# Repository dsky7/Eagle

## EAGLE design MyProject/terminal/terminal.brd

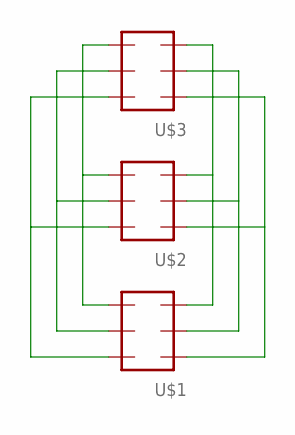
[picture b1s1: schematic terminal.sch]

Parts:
U$1, U$2, U$3: PIN_HEADER_32; PIN_HEADER_3*2

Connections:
unnamed: U$1.P$3 (3), U$2.P$3 (3), U$3.P$3 (3)
unnamed: U$1.P$2 (2), U$2.P$2 (2), U$3.P$2 (2)
unnamed: U$1.P$1 (1), U$2.P$1 (1), U$3.P$1 (1)
unnamed: U$1.P$6 (6), U$2.P$6 (6), U$3.P$6 (6)
unnamed: U$1.P$5 (5), U$2.P$5 (5), U$3.P$5 (5)
unnamed: U$1.P$4 (4), U$2.P$4 (4), U$3.P$4 (4)

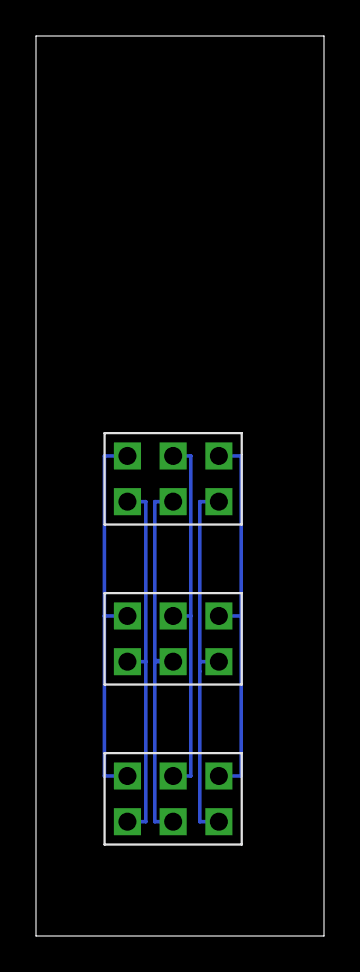
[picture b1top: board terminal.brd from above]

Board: 2 copper layers, 16.0 x 50.0 mm, 3 parts (0 on the bottom side), 6 nets.

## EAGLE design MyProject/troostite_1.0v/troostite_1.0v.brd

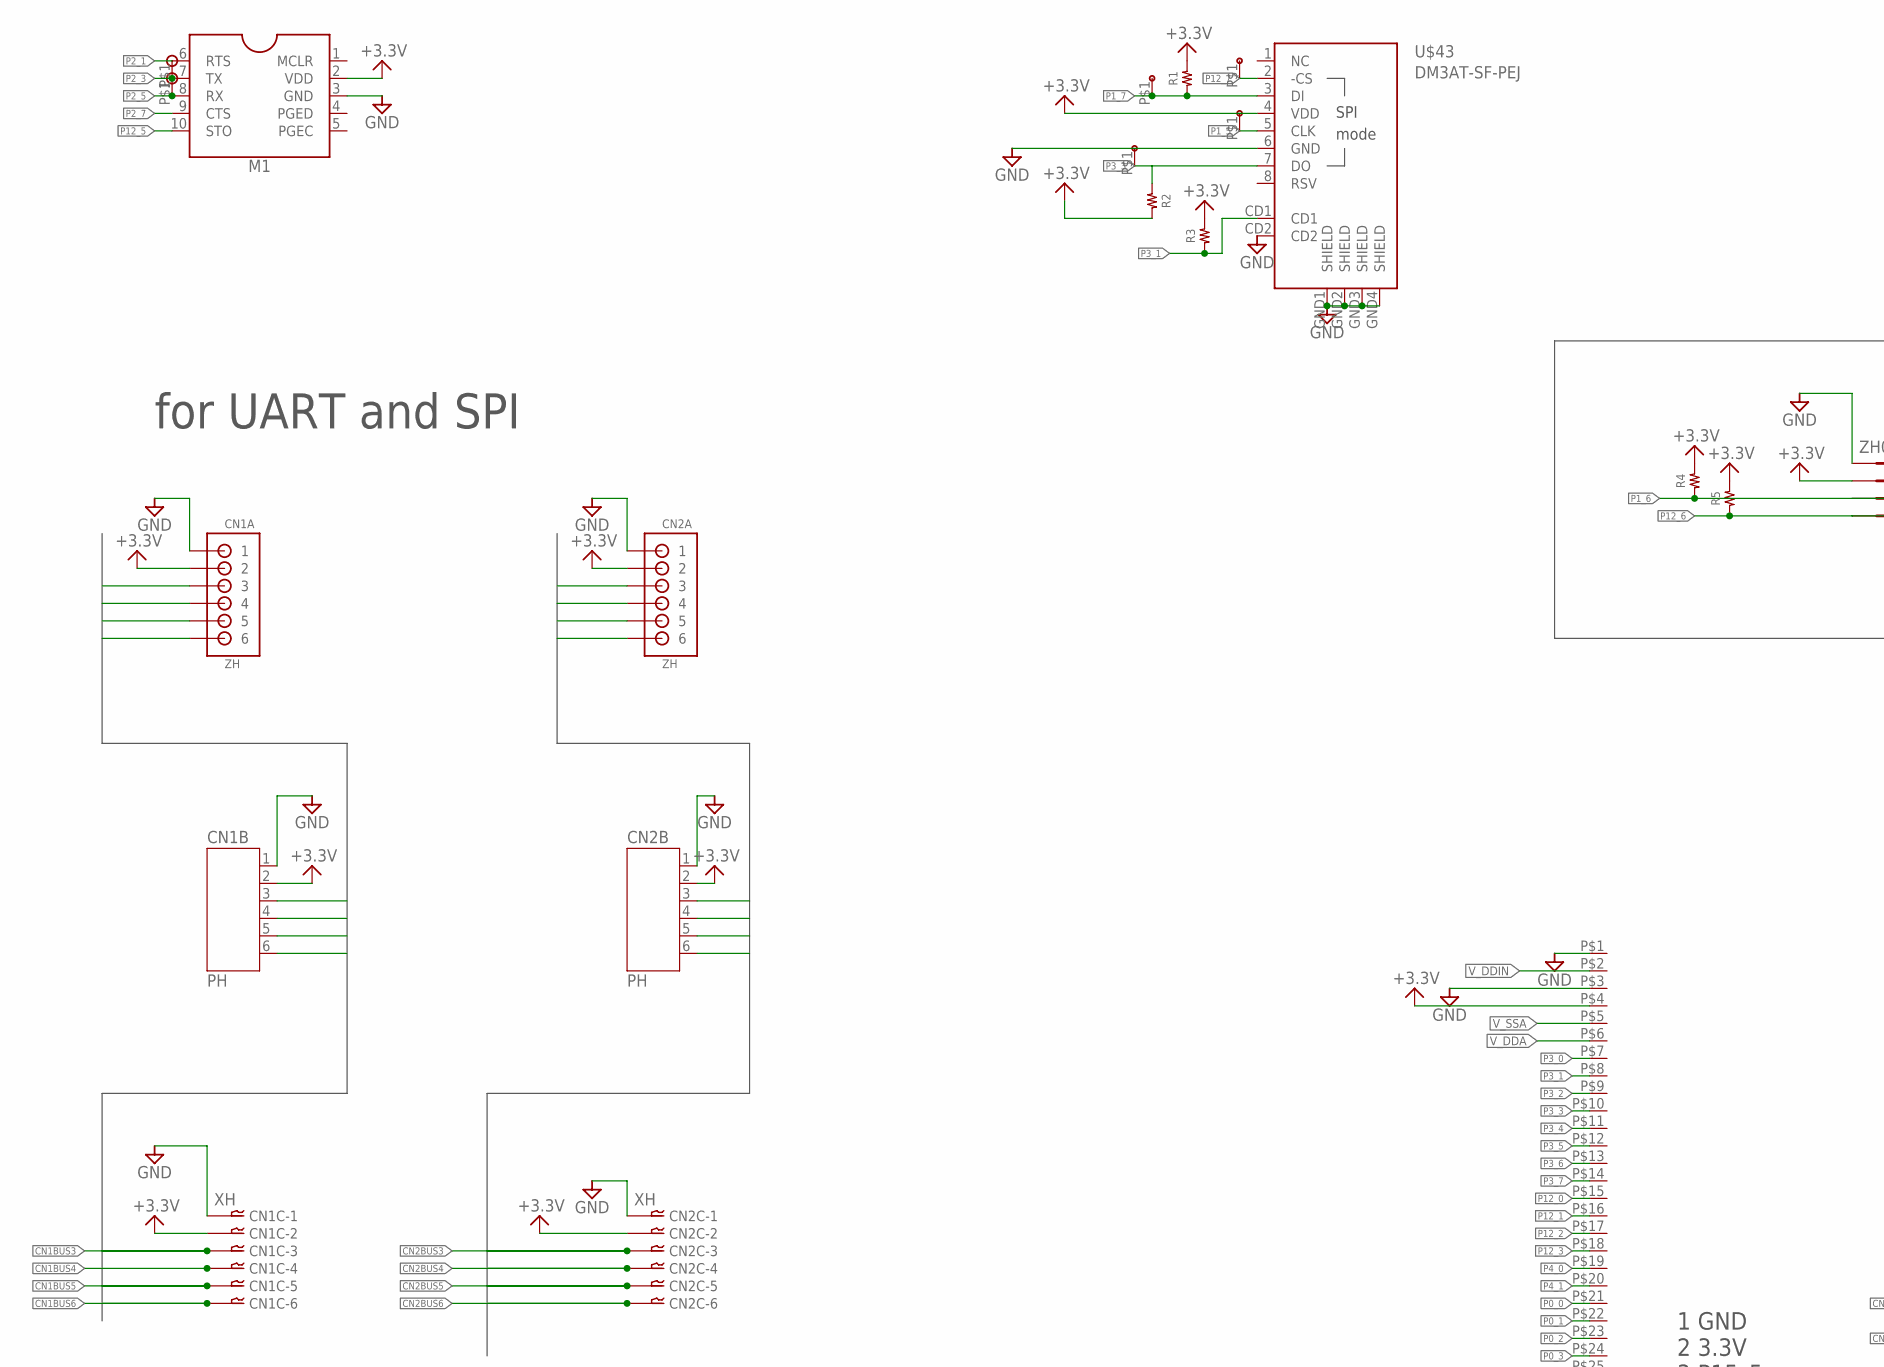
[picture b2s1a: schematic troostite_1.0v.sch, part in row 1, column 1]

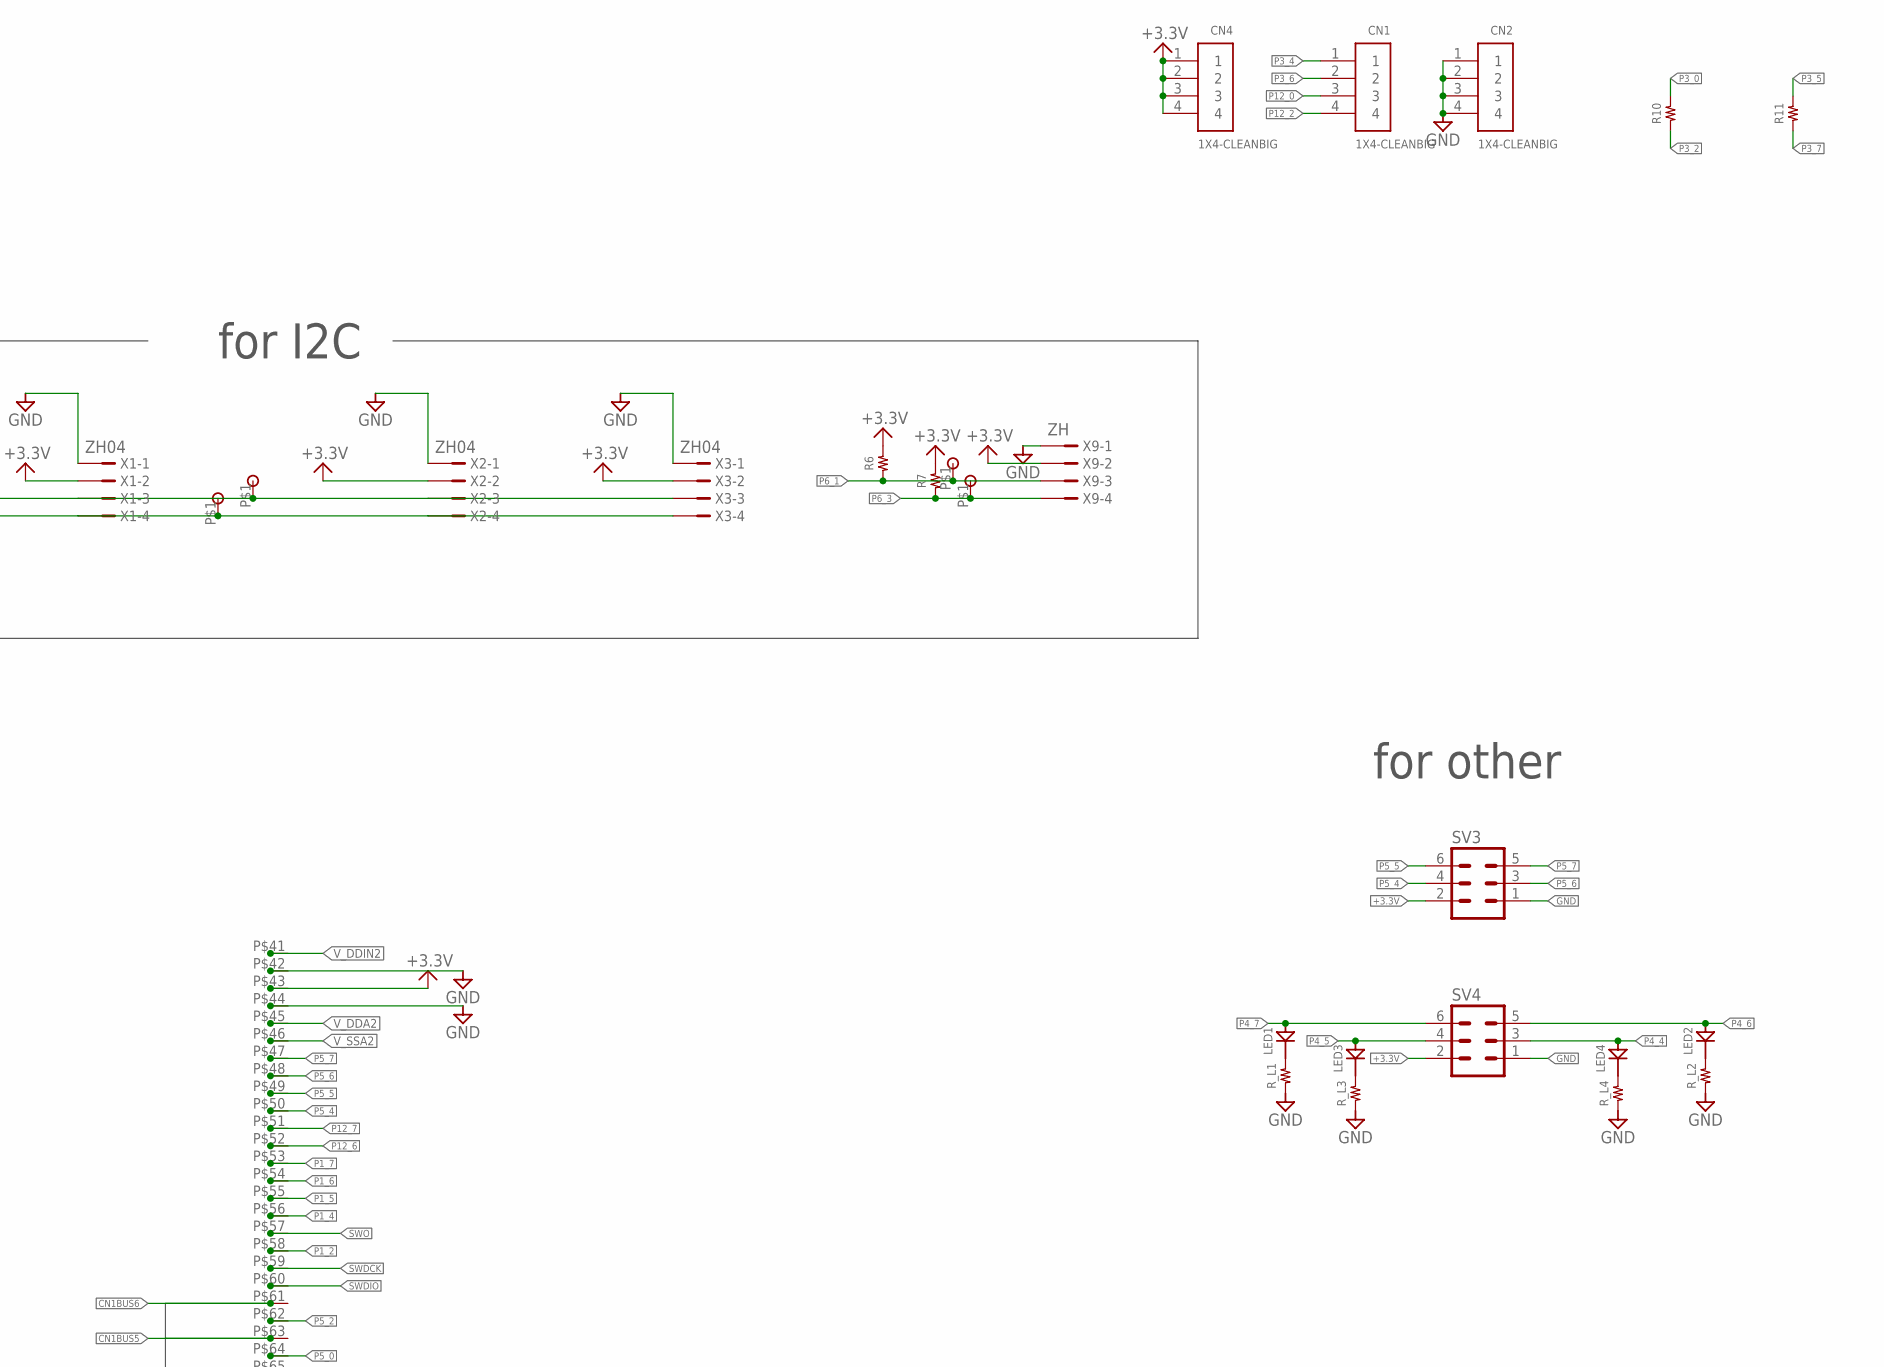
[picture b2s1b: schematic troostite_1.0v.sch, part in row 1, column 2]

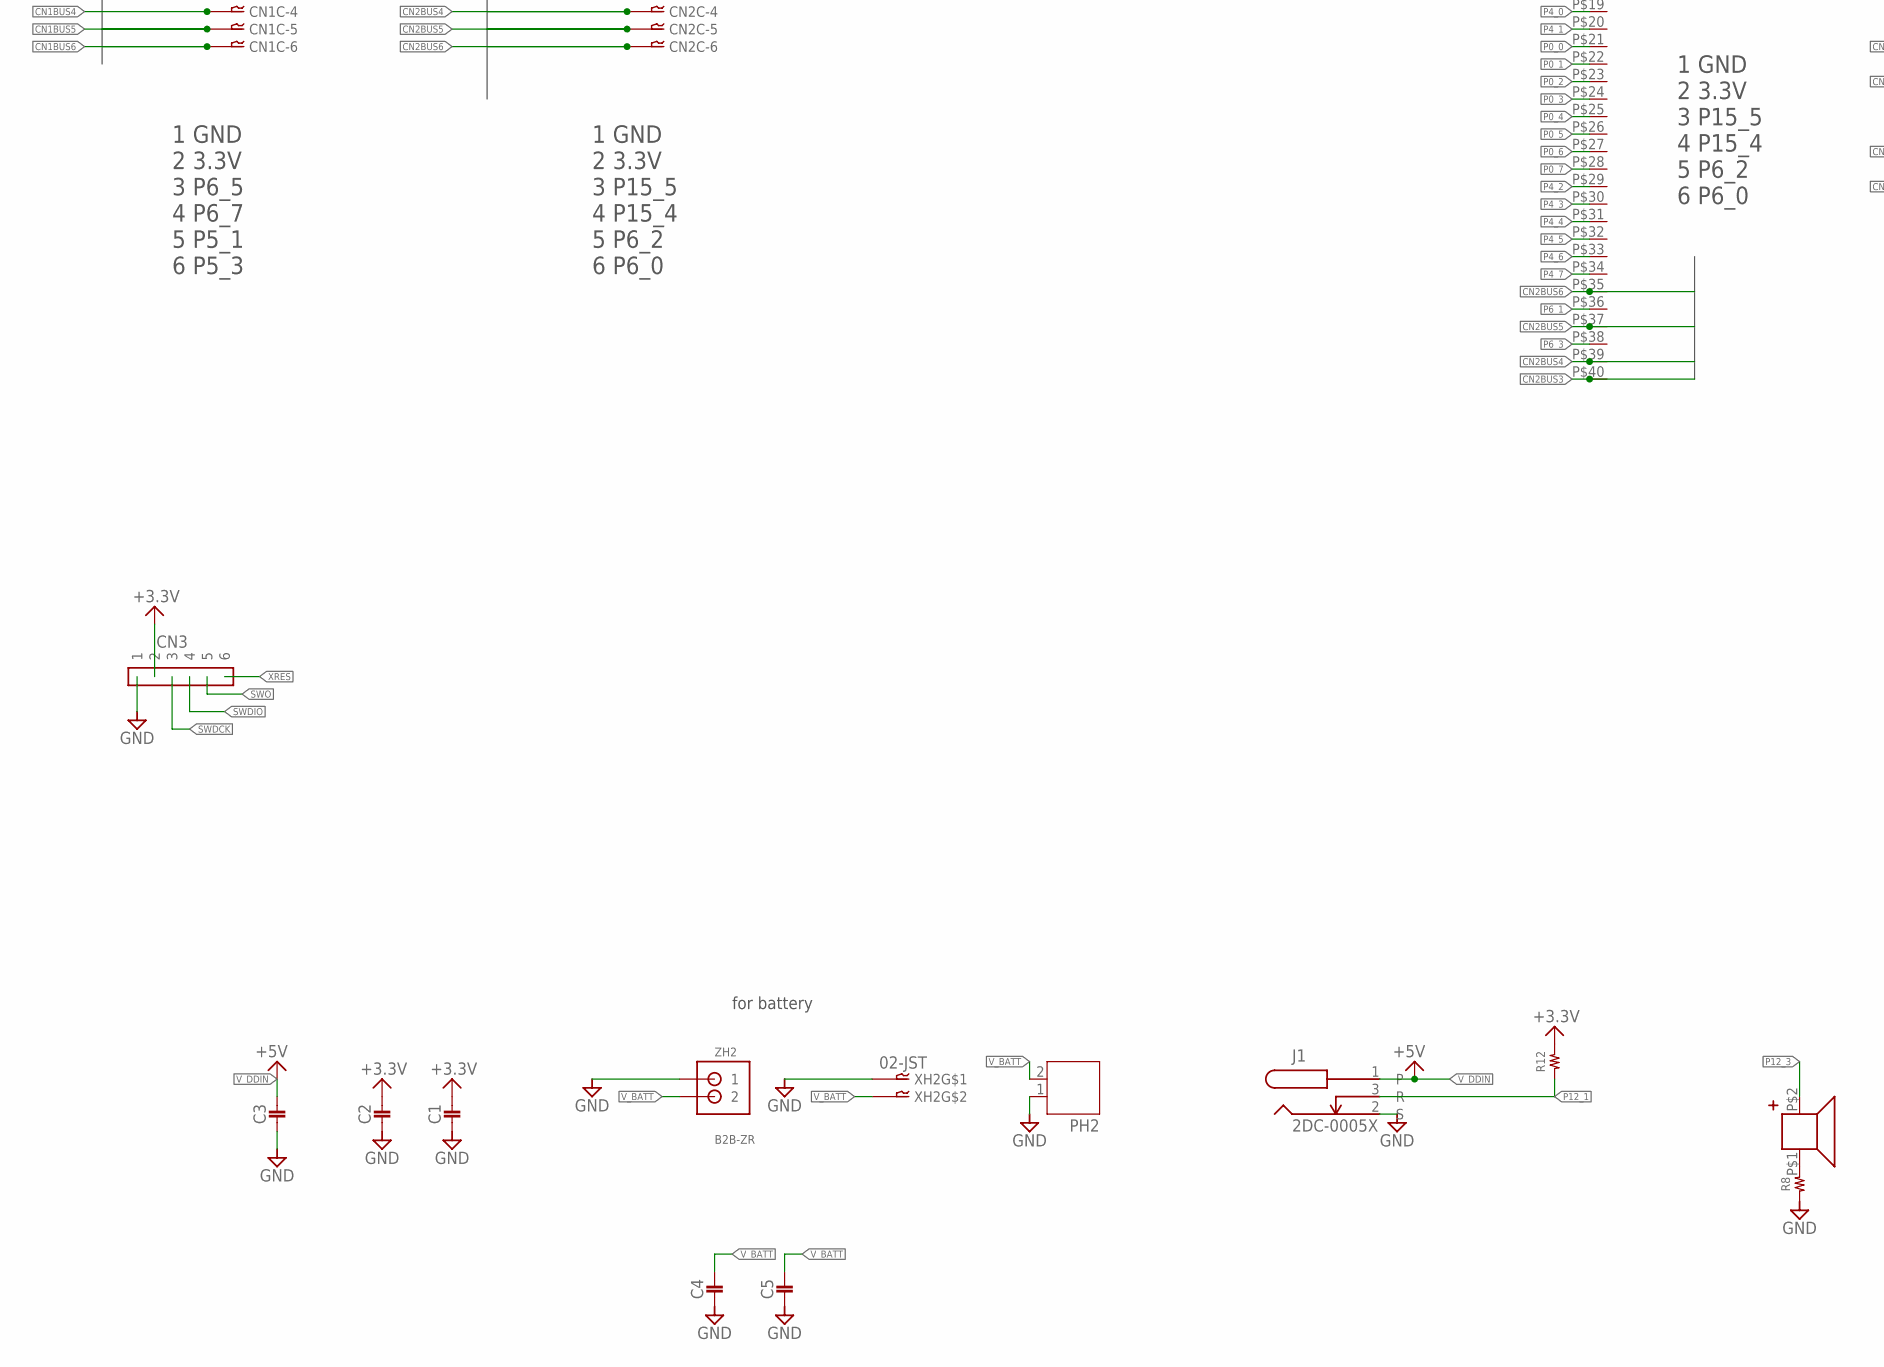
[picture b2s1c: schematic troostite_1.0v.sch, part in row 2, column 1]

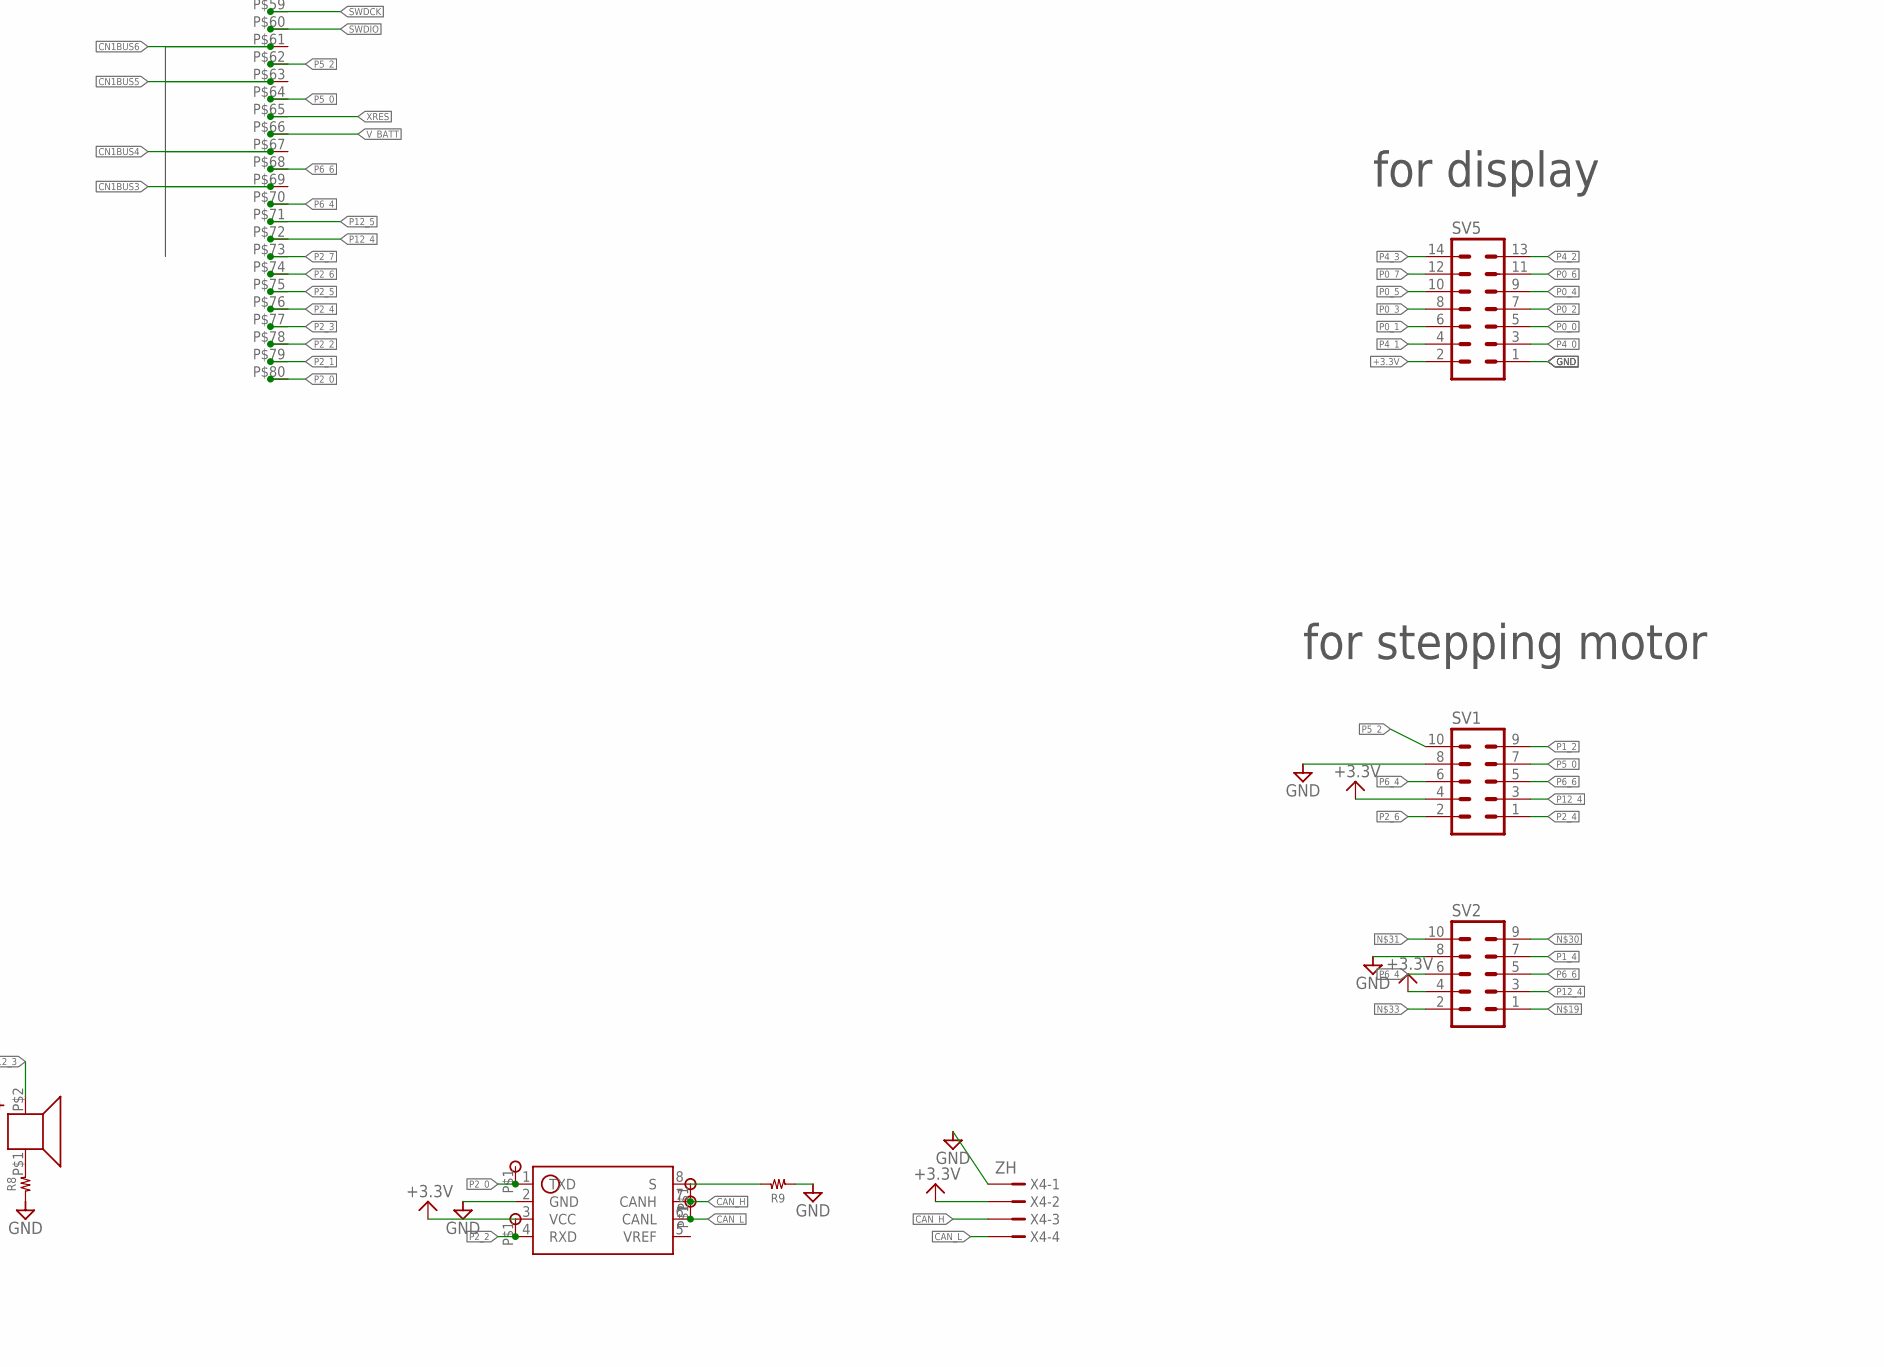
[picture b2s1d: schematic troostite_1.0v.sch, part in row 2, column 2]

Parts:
C1, C2, C3, C4: 1608
C5: 3225
CN1, CN2, CN4: 1X4-CLEANBIG; 1X04-CLEANBIG
CN1A, CN2A: ZH; B6B-ZR
CN1B, CN2B: PH; JST-PH6
CN1C, CN2C: XH; B6B-XH
CN3: PIN_HEADER_6
IC1: SN65HVD1050; SOIC8
J1: 2DC-0005X; 2DC-0005D
LED1, LED2, LED3, LED4: CHIPLED; 1608
M1: SBDBT; DIL10
PH2: JST-PH2
R1, R2, R3, R4, R5, R6, R7, R8, R9, R10, R11, R12: RESISTOR__SMD; 1608
R_L1, R_L2, R_L3, R_L4: RESISTOR__SMD; 1608
SV1, SV2: ML10
SV3, SV4: ML6
SV5: ML14
U$2: PSOC_5LP
U$41: PKLCS1212E4001
U$43: DM3AT-SF-PEJ
U$72, U$73, U$74, U$75, U$76, U$77, U$78, U$79, U$82, U$83: CHECK_0.8MM
U$85, U$86, U$87, U$88: CHECK_21.3; CHECK_2*1.3
X1, X2, X3: ZH04; B4B-ZR
X4, X9: ZH; B4B-ZR
XH2: 02-JST; B2B-XH
ZH2: B2B-ZR

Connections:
+3.3V: C1.P$1 (1), C2.P$1 (1), CN1A.2, CN1B.2, CN1C.P$2, CN2A.2, CN2B.2, CN2C.P$2, CN3.2, CN4.1, CN4.2, CN4.3, CN4.4, IC1.3 (VCC), M1.2 (VDD), R1.2, R2.2, R3.2, R4.2, R5.2, R6.2, R7.2, R12.2, SV1.4, SV2.4, SV3.2, SV4.2, SV5.2, U$2.P$4, U$2.P$43, U$43.4 (VDD), X1.2, X2.2, X3.2, X4.2, X9.2
CAN_H: IC1.7 (CANH), U$72.P$1, X4.3
CAN_L: IC1.6 (CANL), U$73.P$1, X4.4
CN1BUS3: CN1A.3, CN1B.3, CN1C.P$3, U$2.P$69
CN1BUS4: CN1A.4, CN1B.4, CN1C.P$4, U$2.P$67
CN1BUS5: CN1A.5, CN1B.5, CN1C.P$5, U$2.P$63
CN1BUS6: CN1A.6, CN1B.6, CN1C.P$6, U$2.P$61
CN2BUS3: CN2A.3, CN2B.3, CN2C.P$3, U$2.P$40
CN2BUS4: CN2A.4, CN2B.4, CN2C.P$4, U$2.P$39
CN2BUS5: CN2A.5, CN2B.5, CN2C.P$5, U$2.P$37
CN2BUS6: CN2A.6, CN2B.6, CN2C.P$6, U$2.P$35
GND: C1.P$2 (2), C2.P$2 (2), C3.P$2 (2), C4.P$2 (2), C5.P$2 (2), CN1A.1, CN1B.1, CN1C.P$1, CN2.1, CN2.2, CN2.3, CN2.4, CN2A.1, CN2B.1, CN2C.P$1, CN3.1, IC1.2 (GND), J1.2 (S), M1.3 (GND), PH2.1, R8.1, R9.1, R_L1.1, R_L2.1, R_L3.1, R_L4.1, SV1.8, SV2.8, SV3.1, SV4.1, SV5.1, U$2.P$1, U$2.P$3, U$2.P$42, U$2.P$44, U$43.6 (GND), U$43.CD2, U$43.GND1 (SHIELD), U$43.GND2 (SHIELD), U$43.GND3 (SHIELD), U$43.GND4 (SHIELD), X1.1, X2.1, X3.1, X4.1, X9.1, XH2.P$1, ZH2.1
unnamed: R8.2, U$41.P$1 (MINUS)
unnamed: LED1.2 (K), R_L1.2
unnamed: LED3.2 (K), R_L3.2
unnamed: LED4.2 (K), R_L4.2
unnamed: LED2.2 (K), R_L2.2
unnamed: IC1.8 (S), R9.2
P0_0: SV5.5, U$2.P$21
P0_1: SV5.6, U$2.P$22
P0_2: SV5.7, U$2.P$23
P0_3: SV5.8, U$2.P$24
P0_4: SV5.9, U$2.P$25
P0_5: SV5.10, U$2.P$26
P0_6: SV5.11, U$2.P$27
P0_7: SV5.12, U$2.P$28
P1_2: SV1.9, U$2.P$58
P1_4: SV2.7, U$2.P$56
P1_5: U$2.P$55, U$43.5 (CLK), U$87.P$1
P1_6: R4.1, U$2.P$54, U$76.P$1, X1.3, X2.3, X3.3
P1_7: R1.1, U$2.P$53, U$43.3 (DI), U$85.P$1
P2_0: IC1.1 (TXD), U$2.P$80, U$74.P$1
P2_1: M1.6 (RTS), U$2.P$79
P2_2: IC1.4 (RXD), U$2.P$78, U$75.P$1
P2_3: M1.7 (TX), U$2.P$77, U$82.P$1
P2_4: SV1.1, U$2.P$76
P2_5: M1.8 (RX), U$2.P$75, U$83.P$1
P2_6: SV1.2, U$2.P$74
P2_7: M1.9 (CTS), U$2.P$73
P3_0: R10.2, U$2.P$7
P3_1: R3.1, U$2.P$8, U$43.CD1
P3_2: R10.1, U$2.P$9
P3_3: R2.1, U$2.P$10, U$43.7 (DO), U$88.P$1
P3_4: CN1.1, U$2.P$11
P3_5: R11.2, U$2.P$12
P3_6: CN1.2, U$2.P$13
P3_7: R11.1, U$2.P$14
P4_0: SV5.3, U$2.P$19
P4_1: SV5.4, U$2.P$20
P4_2: SV5.13, U$2.P$29
P4_3: SV5.14, U$2.P$30
P4_4: LED4.1 (A), SV4.3, U$2.P$31
P4_5: LED3.1 (A), SV4.4, U$2.P$32
P4_6: LED2.1 (A), SV4.5, U$2.P$33
P4_7: LED1.1 (A), SV4.6, U$2.P$34
P5_0: SV1.7, U$2.P$64
P5_2: SV1.10, U$2.P$62
P5_4: SV3.4, U$2.P$50
P5_5: SV3.6, U$2.P$49
P5_6: SV3.3, U$2.P$48
P5_7: SV3.5, U$2.P$47
P6_1: R6.1, U$2.P$36, U$78.P$1, X9.3
P6_3: R7.1, U$2.P$38, U$79.P$1, X9.4
P6_4: SV1.6, SV2.6, U$2.P$70
P6_6: SV1.5, SV2.5, U$2.P$68
P12_0: CN1.3, U$2.P$15
P12_1: J1.3 (R), R12.1, U$2.P$16
P12_2: CN1.4, U$2.P$17
P12_3: U$2.P$18, U$41.P$2 (PLUS)
P12_4: SV1.3, SV2.3, U$2.P$72
P12_5: M1.10 (STO), U$2.P$71
P12_6: R5.1, U$2.P$52, U$77.P$1, X1.4, X2.4, X3.4
P12_7: U$2.P$51, U$43.2 (-CS), U$86.P$1
SWDCK: CN3.3, U$2.P$59
SWDIO: CN3.4, U$2.P$60
SWO: CN3.5, U$2.P$57
V_BATT: C4.P$1 (1), C5.P$1 (1), PH2.2, U$2.P$66, XH2.P$2, ZH2.2
V_DDA: U$2.P$6
V_DDA2: U$2.P$45
V_DDIN: C3.P$1 (1), J1.1, U$2.P$2
V_DDIN2: U$2.P$41
V_SSA: U$2.P$5
V_SSA2: U$2.P$46
XRES: CN3.6, U$2.P$65

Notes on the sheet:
for stepping motor
for other
for battery
for UART and SPI
for I2C
for display
1 GND 2 3.3V 3 P6_5 4 P6_7 5 P5_1 6 P5_3
1 GND 2 3.3V 3 P15_5 4 P15_4 5 P6_2 6 P6_0

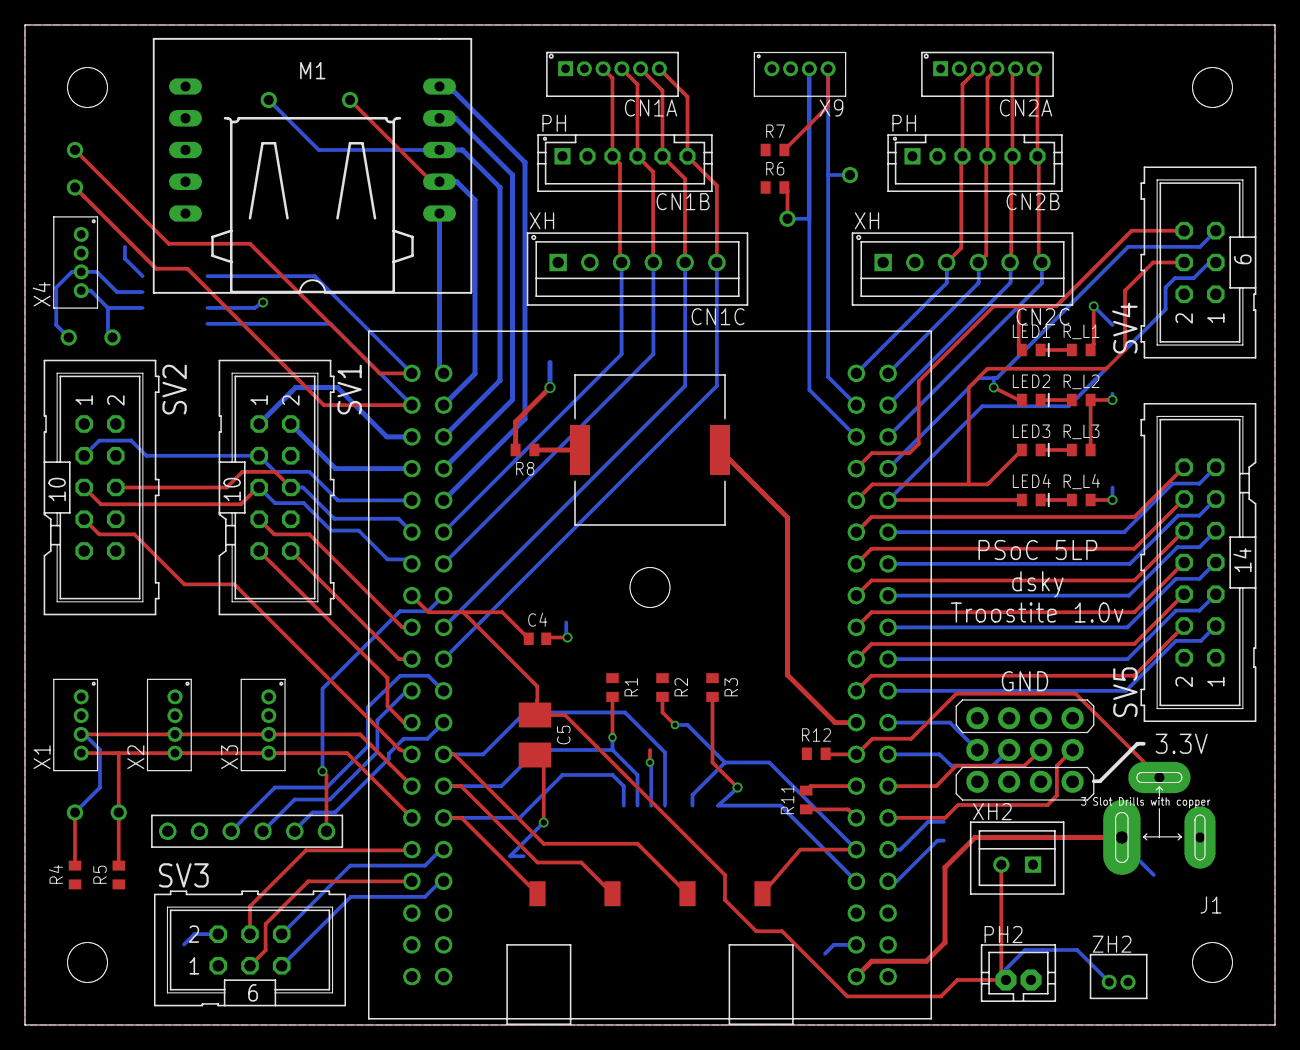
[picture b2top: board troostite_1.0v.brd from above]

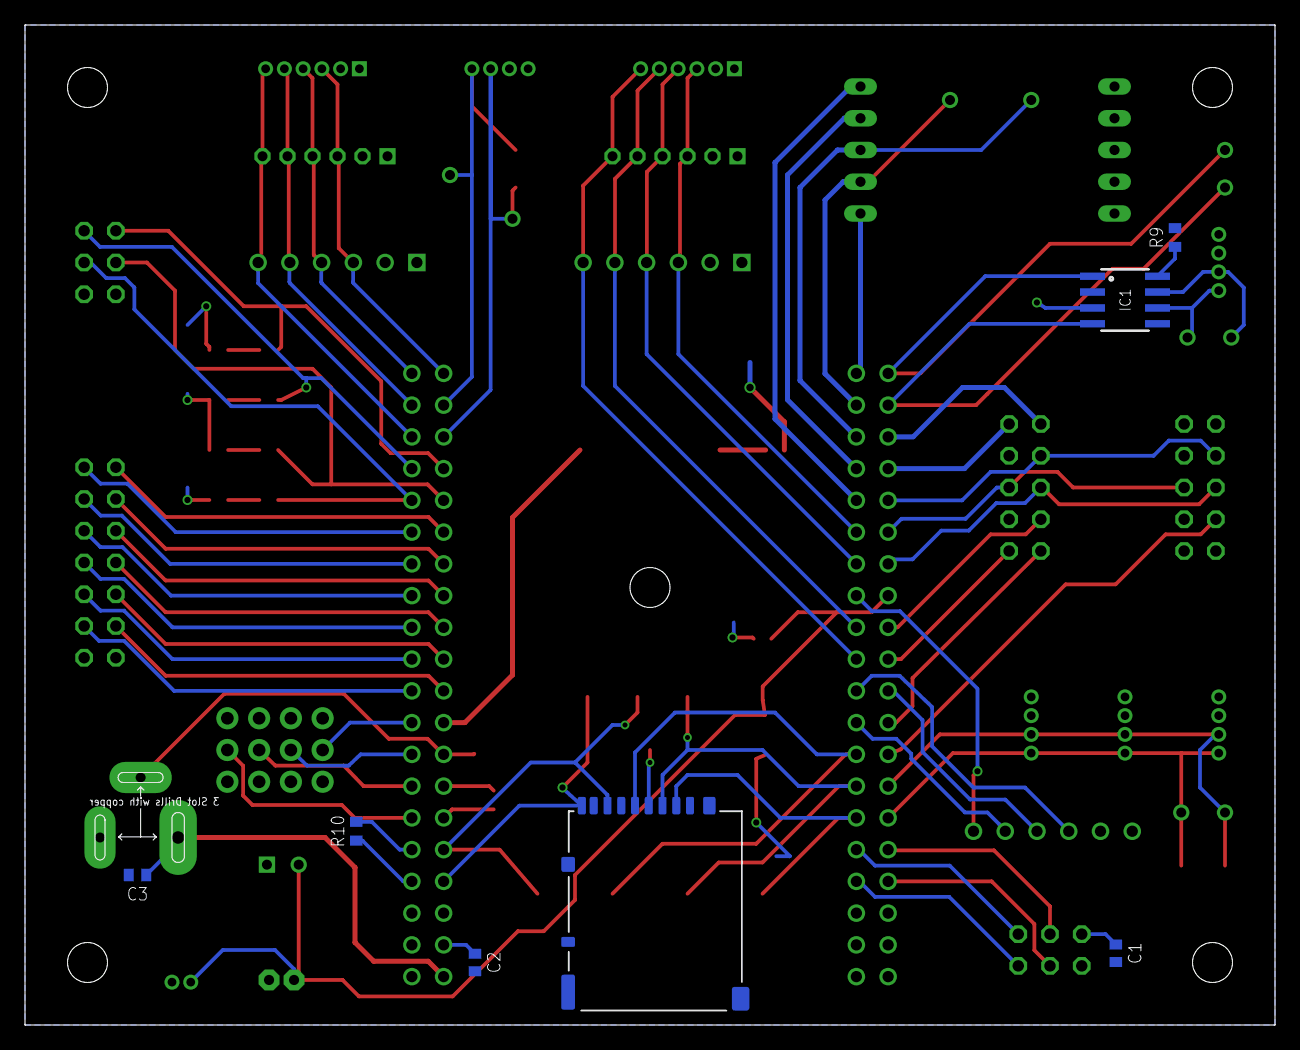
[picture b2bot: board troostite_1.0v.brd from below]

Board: 2 copper layers, 100.0 x 80.0 mm, 68 parts (7 on the bottom side), 79 nets.
